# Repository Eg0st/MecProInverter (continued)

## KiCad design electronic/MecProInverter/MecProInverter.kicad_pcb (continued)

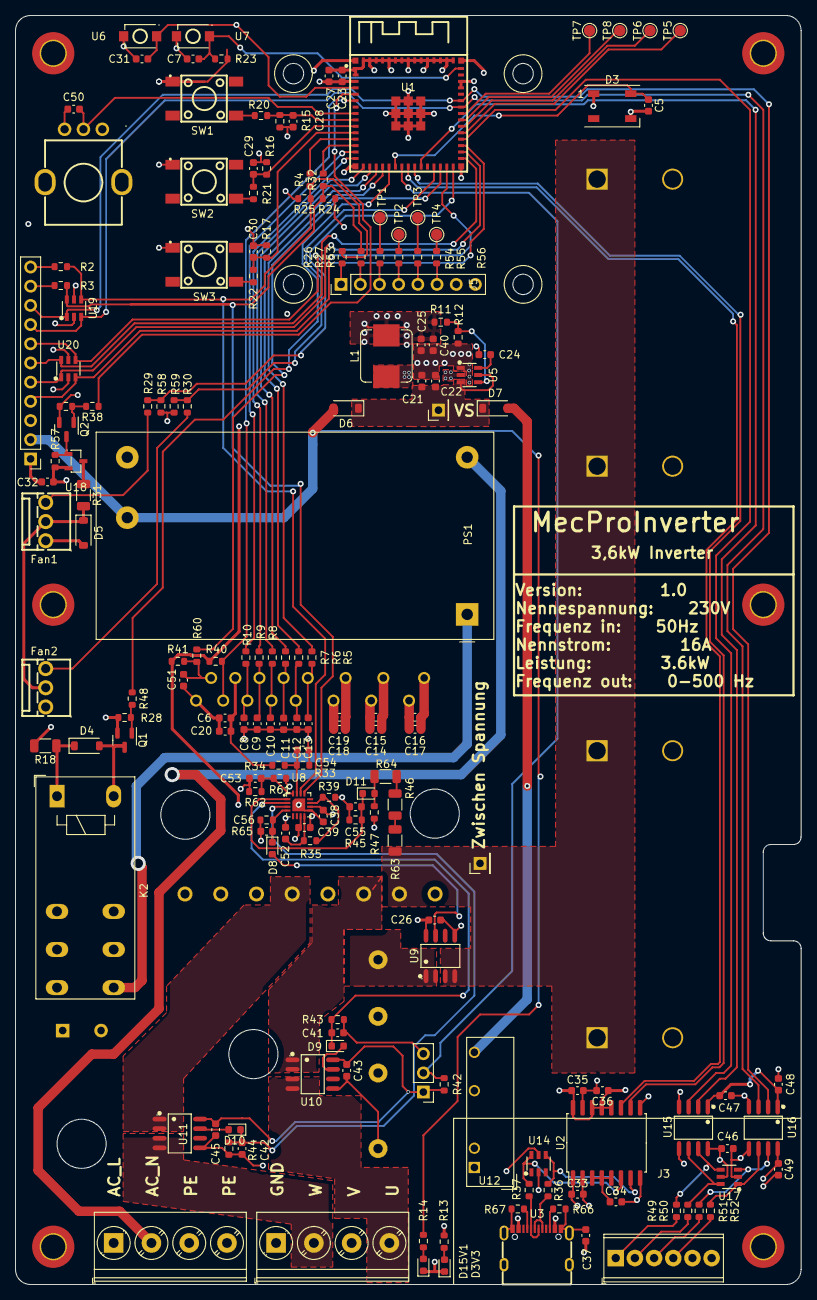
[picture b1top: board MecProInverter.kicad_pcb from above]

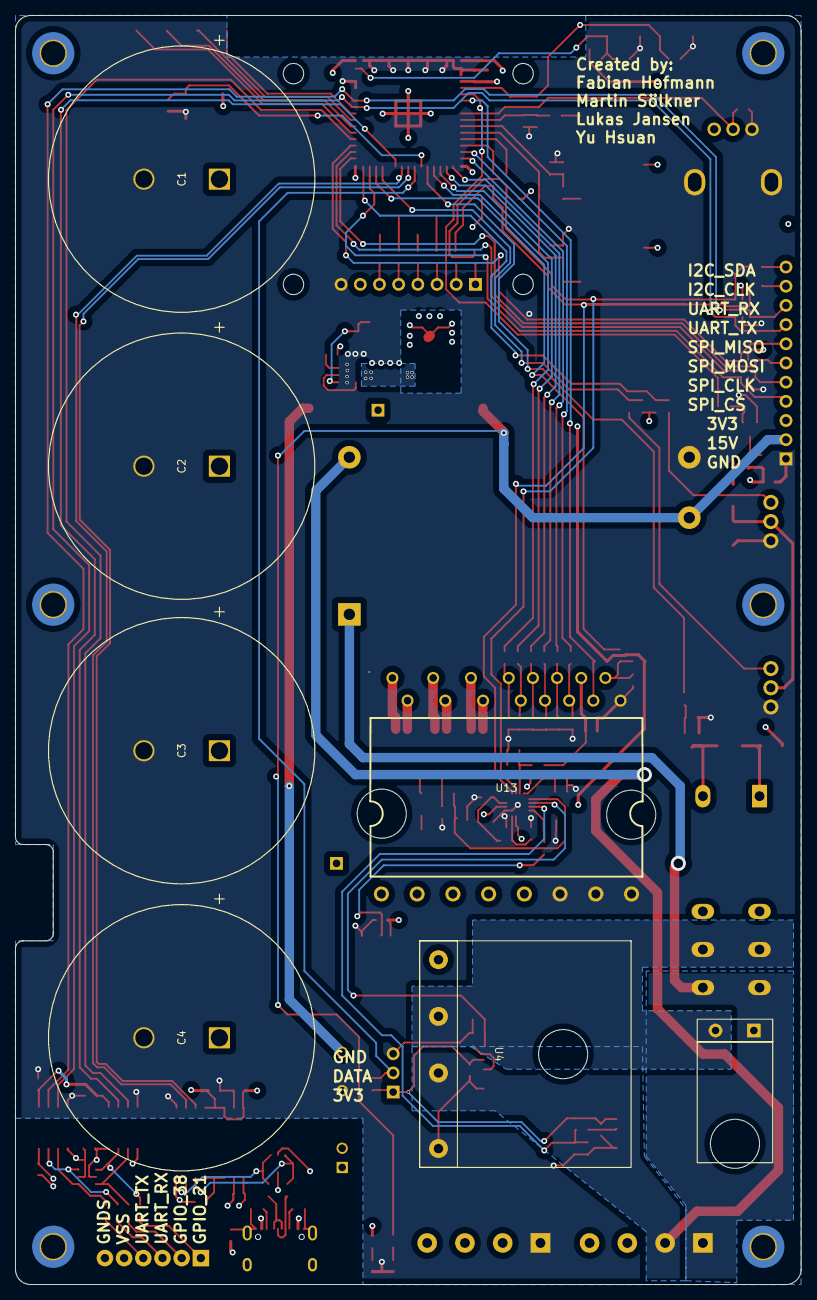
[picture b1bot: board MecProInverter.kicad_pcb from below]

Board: 4 copper layers, 104.0 x 168.0 mm, 186 parts (7 on the bottom side), 129 nets.

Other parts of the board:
D3V3: LED_3.3V; LED_0603_1608Metric
D15V1: LED_15V; LED_0603_1608Metric
Q2: DMN3404L; SOT-23

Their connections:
GND: D3V3.1 (K), D15V1.1 (K), Q2.2 (S); also elsewhere on the board
unnamed 42: D3V3.2 (A); also elsewhere on the board
unnamed 52: D15V1.2 (A); also elsewhere on the board

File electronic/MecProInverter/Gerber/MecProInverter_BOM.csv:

1;"C49,C23,C35,C5,C54,C45,C56,C41,C43,C24,C55,C42,C47,C15,C46,C48,C51,C6,C19,C26,C33,C53,C34,C21,C36,C16";"C_0603_1608Metric";26;"100nF";
2;"TP1,TP2,TP3,TP4";"TestPoint_Pad_D1.5mm";4;"TestPoint";
3;"R19,R57,R23,R62,R40,R58,R59,R12,R34";"R_0603_1608Metric";9;"10k";
4;"D8,D9,D10,D11";"D_0603_1608Metric";4;"D";
5;"C25,C27,C40";"C_0603_1608Metric";3;"22uF";
6;"C22,C37,C20";"C_0603_1608Metric";3;"10uF";
7;"C18,C14,C17";"C_0603_1608Metric";3;"4.7uF";
8;"R29,R26,R4,R2,R27,R30,R32,R3";"R_0603_1608Metric";8;"121";
9;"Fan1,Fan2";"CONN-TH_3P-P2.54_22-23-2031";2;"0022232031";
10;"U12";"Converter_DCDC_TRACO_TEA1HI-xxxx_THT";1;"TEA1-0505HI";
11;"U20,U14,U19,U17";"SOT-23-6_L2.9-W1.6-P0.95-LS2.8-BL";4;"PSRV05-4MR6T1G";
12;"C11,C8,C9,C13,C10,C12";"C_0603_1608Metric";6;"10nF";
13;"SW2,SW1,SW3";"KEY-SMD_4P-L6.1-W6.1-P4.50-LS9.0";3;"PTS645SM95SMTR92LFS";
14;"R64,R63,R46";"R_1206_3216Metric";3;"33k";
15;"R54,R55,R53,R56";"R_0603_1608Metric";4;"0";
16;"J7";"PinHeader_1x11_P2.54mm_Vertical";1;"Test";
17;"Q1,Q2";"SOT-23";2;"DMN3404L";
18;"C30,C31,C32,C7,C29,C28,C50,C52";"C_0603_1608Metric";8;"1uF";
19;"H1,H6,H5,H4,H2,H3";"MountingHole_3.2mm_M3_DIN965_Pad_TopBottom";6;"~";
20;"D3";"LED_WS2812B_PLCC4_5.0x5.0mm_P3.2mm";1;"WS2812B";
21;"R49,R50,R51,R52";"R_0603_1608Metric";4;"180";
22;"R31";"R_1206_3216Metric";1;"0";
23;"K2";"Relay_SPDT_Schrack-RT1-16A-FormC_RM5mm";1;"RT314A12";
24;"R14,R47";"R_0603_1608Metric";2;"820";
25;"U18";"SOT-23-3_L2.9-W1.3-P1.90-LS2.3-BR";1;"PMV100EPAR";
26;"D6,D4,D5,D7";"D_SOD-123";4;"D";
27;"R66,R67";"R_0603_1608Metric";2;"5.1k";
28;"R8,R10,R48,R6,R9,R38,R5,R7";"R_0603_1608Metric";8;"165";
29;"J4";"TerminalBlock_Phoenix_PT-1,5-4-5.0-H_1x04_P5.00mm_Horizontal";1;"Motor";
30;"R11";"R_0603_1608Metric";1;"33.2k";
31;"C38,C39";"C_0603_1608Metric";2;"220nF";
32;"R35";"R_0603_1608Metric";1;"999M";
33;"R41";"R_0603_1608Metric";1;"4,7k";
34;"U7,U6";"SW-SMD_L3.9-W3.0-P4.45";2;"SKRKAEE020";
35;"U5";"SOT-23-6_L2.9-W1.6-P0.95-LS2.8-BL";1;"TPS563201DDCR";
36;"R17,R15,R16";"R_0603_1608Metric";3;"100K";
37;"J3";"TerminalBlock_Phoenix_MPT-0,5-6-2.54_1x06_P2.54mm_Horizontal";1;"ISO_Data";
38;"U3";"USB-C-SMD_TYPE-C-6PIN-2MD-073";1;"TYPE-C_16PIN_2MD(073)";
39;"U2";"SOIC-16W_7.5x10.3mm_P1.27mm";1;"ADUM3160";
40;"R37,R36";"R_0603_1608Metric";2;"24";
41;"U15,U16";"SOIC-8_L4.9-W3.9-P1.27-LS6.0-BL";2;"ADUM1201ARZ-RL7";
42;"R18";"R_1206_3216Metric";1;"90";
43;"R44,R43,R65,R45";"R_0603_1608Metric";4;"10M";
44;"J8";"PinHeader_1x01_P2.54mm_Vertical";1;"U_ZK";
45;"D1";"LED_0603_1608Metric";1;"LED_3.3V";
46;"R33";"R_0603_1608Metric";1;"1.8k";
47;"TP5";"TestPoint_Pad_D1.5mm";1;"MTCK";
48;"R24,R25";"R_0603_1608Metric";2;"1.6k";
49;"TP8";"TestPoint_Pad_D1.5mm";1;"MTDI";
50;"U10,U11,U9";"SOP-8_L4.9-W3.9-P1.27-LS6.0-BL";3;"CC6904SO-30A";
51;"R42";"R_0603_1608Metric";1;"4.7k";
52;"J5";"Adafruit_938";1;"Display";
53;"J9";"PinHeader_1x01_P2.54mm_Vertical";1;"U_VS";
54;"U8";"WQFN-16_L3.0-W3.0-P0.50-TL-EP1.7";1;"TLA2528IRTER";
55;"R13";"R_0603_1608Metric";1;"40";
56;"R28";"R_0603_1608Metric";1;"100k";
57;"R39";"R_0603_1608Metric";1;"33k";
58;"R60";"R_0603_1608Metric";1;"330";
59;"R20,R21";"R_0603_1608Metric";2;"1K";
60;"U21";"RES-ADJ-TH_RK09D1130C4G";1;"RK09D113000F_10k";
61;"D2";"LED_0603_1608Metric";1;"LED_15V";
62;"L1";"L_Bourns_SRP7028A_7.3x6.6mm";1;"2.2uH";
63;"J10";"TerminalBlock_Phoenix_PT-1,5-4-5.0-H_1x04_P5.00mm_Horizontal";1;"Net";
64;"R22";"R_0603_1608Metric";1;"1k";
65;"TP6";"TestPoint_Pad_D1.5mm";1;"MTDO";
66;"TP7";"TestPoint_Pad_D1.5mm";1;"MTMS";
67;"R61";"R_0603_1608Metric";1;"3.3k";
68;"U1";"BULETM-SMD_ESP32-S3-MINI-1-N8";1;"ESP32-S3-MINI-1-N8";
69;"J6";"PinHeader_1x03_P2.54mm_Vertical";1;"MAX312820";
70;"PS1";"Converter_ACDC_MeanWell_IRM-20-xx_THT";1;"IRM-20-15";
71;"R1";"PWR220T-20";1;"14.4";
72;"C2,C1,C4,C3";"ESMQ351VSN102MA50S";4;"1mF";
73;"U13";"DIP-24_L36.0-W21.0-P1.60-LS28.6-TL";1;"IKCM20L60GA";
74;"U4";"LVE2560E";1;" LVE2560E";

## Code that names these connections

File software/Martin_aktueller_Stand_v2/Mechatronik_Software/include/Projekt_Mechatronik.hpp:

#ifndef MAIN_H
#define MAIN_H

//include Dateien
#include <Arduino.h>
#include <stdlib.h>
#include <stdio.h>
#include <Wire.h>
#include "Sensor_Funktionen.hpp"
#include "Adafruit_SSD1306.h"
#include "state_machine.hpp"
#include "Sinus_Generatur.hpp"
#include <SimpleFOC.h>


//namespaces
using namespace std;

// Definitionen für den Display
#define SSD1306_I2C_ADDR 0x3D
#define SCREEN_WIDTH 128 // OLED display width, in pixels
#define SCREEN_HEIGHT 64 // OLED display height, in pixels
#define WIRE_MAX 32

// Definitionen der Konstanten für den Temperatursensor
// Data wire is connected to GPIO 4
#define ONE_WIRE_BUS 4

//Definitionen der Ein-/Ausgaenge
#define PIN_IPH1 A15 //ADC2_5 == A15
#define PIN_IPH2 A16 //ADC2_6 == A16 
#define PIN_IPH3 A17 //ADC2_7 == A17

#define HALL_PH1 19
#define HALL_PH2 18
#define HALL_PH3 5

#define PIN_PH1_H 18 // 23
#define PIN_PH2_H 17 // 1
#define PIN_PH3_H 32
#define PIN_PH1_L 33
#define PIN_PH2_L 25
#define PIN_PH3_L 26

#define FAN_CONTROL_PIN 1
#define VFO 2
#define POT1 4
#define SW1 5
#define SW2 6
#define SW3 7
#define I2C_SDA 8
#define I2C_SLK 9

#define LINW 10
#define LINV 11
#define LINU 12
#define HINW 13
#define HINV 14
#define HINU 15

#define RELAY_SHUNT_AC 16
#define RGBLED 17
#define TEMP_HEATSINK 18

#define UART_TX 00
#define UART_RX 00

#define USB_N 19
#define USB_P 20

#define ISO_GPIO_1 21
#define ISO_GPIO_2 38

#define I_TRIP 28
#define SPI_CS 34
#define SPI_MOSI 35
#define SPI_CLK 36
#define SPI_MISO 37

#define FAN1_PWM_FB 48
#define FAN2_PWM_FB 47

#endif

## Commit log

2023-10-19 init
    init
2023-10-24 documentation
    added bestellliste
2023-10-25 ssd1306_bib
    library to controll an adafruit oled display
2023-10-26 docu
    Projektplan
2023-11-02 docu
    ssd1306 in software verschoben
2023-11-02 docu
    added mechanic
2023-11-04 electronic
    library added
2023-11-04 electronic
    Test .gitignore (venv)
2023-11-05 Create Prinzipschaubild
2023-11-05 electronic
    library expanded
2023-11-07 electronic
    - power: added 3.3V coverter
    - power: added bridge rectifier
    - power: added half bridge
2023-11-10 electronic
    -power: added 15/3,3 Volt voltage regulator
    - power: added power relay
    - control: added USB-ISO, added User interface
2023-11-14 electronic
2023-11-14 Create FST_TEST
2023-11-14 FST_TEST
2023-11-17 FSM
    Funktionierende Klasse für eine State Machine:
    TState_Machine: allgemeines Template für eine FSM
    states: States die benutzt werden
    state_machine: Spezialisierung
2023-11-20 electronic
    -Control: Added Temp, Fan,
2023-11-21 Sinus_Generator
    Creates a LUT for a sine
2023-11-22 aktueller Stand
2023-11-23 Update_Zustandsdiagramm
2023-11-24 electronic
    Added: current sensor
2023-11-28 Electronic
    Currentsensor updated
    Power structure updated
2023-11-29 Electronic
    Rework: Fan, ESP32 Pinout, 15V Power,
    Added: GPIO ISO, ESD
2023-11-29 Update_of_state_actual
2023-11-29 Electronic
    Power Terminal edit
2023-11-30 Electronic
    Footprint assignment
2023-11-30 Electronic
    Voltage messurment updated
2023-11-30 Electronic
    docu
2023-12-04 Electronic
    Added 3d Moodel on Layout
2023-12-06 Electronic
    Schematic V1.0
2023-12-06 Electronic
    Added USB-C CC Resistor
2023-12-07 Electronic
    Layout begin
2023-12-07 Electronic
    Generated Step
2023-12-07 Electronic
    Ready to buy
2023-12-13 Electronic
    PCB buy!!!
2023-12-21 New Version
    Implement the sensor namespace to readout the ADC and temp
2023-12-27 Software
    Added Pinout
    Created arduino Hardware Test
2023-12-27 new version
2024-01-11 new version_v4
2024-01-11 Software
    Added LED
2024-01-11 Software
    Added LED
    Added ADC Test
2024-01-11 v5 version
2024-01-19 Version V_7
2024-01-23 Projektberichte
    Elektronik added
2024-01-23 docu
    Added pictures
2024-01-23 Changing Names
2024-01-23 docu
    Pictures: added Inverter.png
2024-01-23 docu
    added Abschlusspräsentation
2024-03-16 Docu
    added picture
